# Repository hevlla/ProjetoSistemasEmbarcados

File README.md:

# Controlador do nível de água

## Introdução:

  O controlador de nível de água, é um projeto cujo objetivo é utilizar um microcontrolador que será o responsável pelo controle automático da bomba de água, mensurando com o auxílio de sensores, o nível de água em um tanque. Este sistema monitora o nível de água do tanque e liga a bomba automaticamente sempre que o tanque está vazio. A bomba é desligada quando o tanque superior ou recipiente está cheio. Aqui, o nível de água do tanque é indicado no LCD (Display de cristal líquido). Usando este sistema, podemos evitar o transbordamento da água.
  O presente trabalho apresenta uma solução prática para solucionar problemas relacionados ao controle do nível de água nos mais diversos reservatórios. Tendo em vista a dificuldade de acesso onde os reservatórios são instalados, em locais altos, torna-se difícil a visualização do seu conteúdo e consequentemente de seu controle; torna-se então indispensável a utilização de um sensor de nível de água não só para facilitar mas como também ao acrescentar a automatização, proporcionar uma melhor experiência para as pessoas que utilizam deste serviço.

## Estado da arte:

  O Sensor de Nível é um tipo de medidor feito para atuar em determinados pontos fixos de nível. Esses pontos fixos são valores de nível que, uma vez alcançados, exigem o desencadeamento de alguma ação necessária para a operação ou para a segurança do sistema em que o instrumento está inserido. Esses sensores podem ser utilizados para ligar uma bomba, acionar um alarme ou desencadear uma sequência de operações automáticas quando o nível atinge um ponto fixo, informando à eles através de ajustes determinados.
  Um Sensor de Nível é composto basicamente de duas partes: um detector de nível e um circuito de saída. O detector informa ao circuito de saída a presença ou ausência do nível em determinada posição. Já o circuito de saída se encarrega de alterar o estado de saída do sensor em função da informação transmitida pelo detector.

  - **Sensor de nível tipo bóia**
    É uma solução simples e amplamente utilizada no mercado devido a sua simplicidade e baixo custo de aplicação. Ele pode ser instalado tanto na horizontal quanto na vertical.  A forma mais utilizada é na parte lateral do tanque, horizontalmente. Quando o nível aumenta ou diminui, a boia se movimenta junto e, através de uma haste, é feito, magneticamente, o acionamento do contato.

  - **Sensor de nível capacitivo**
    Funciona como um capacitor. O sensor é uma das placas do capacitor e a parede metálica do tanque é a segunda. O que está entre eles é o material isolante. 
    A capacitância é a capacidade de armazenamento do capacitor. Isto depende das áreas da placa e de suas distância, além da constante dielétrica. Quando o tanque está com o nível zerado, existe apenas o ar como material isolante entre as placas. À medida que o produto começa a preencher o tanque, a capacitância é alterada. Ela é diretamente proporcional ao nível do tanque.

  - **Sensor de nível vibratório**
    Atua utilizando o amortecimento da vibração de uma haste só ou de duas hastes em forma de diapasão como meio de medir o nível. 
    O amortecimento mecânico acontece pela absorção de energia de vibração pela viscosidade de um líquido ou pela resistência de sólidos granulares ou em pó que entram em contato com uma ou mais hastes.
    O Sensor de Nível por vibração consiste em um garfo simétrico com duas extremidades. Na base do garfo há uma fina membrana com conexão a uma extensão em aço inoxidável que entra em contato com o processo. O garfo de vibração é excitado por uma frequência de ressonância por meio da membrana através de um cristal piezoelétrico.
    O garfo de vibração é projetado para, quando for imerso em um material, haver um deslocamento na sua frequência de ressonância de aproximadamente 10% a 20%. A frequência de ressonância é coletada por um receptor de cristal, e o seu deslocamento por um circuito específico tem por função comutar do tipo NA ou NF.
    De acordo com a configuração em que é executada, o Sensor de Nível vibratório poderá ser instalado lateralmente ou no topo do reservatório. Só é preciso ter cuidado com os cantos onde possam haver acúmulo de material e com as áreas em que ocorre a queda de material para a alimentação do reservatório.

  - Sensor de nível Condutivo
    O funcionamento desse tipo de sensor não possui restrição quanto à alta temperatura ou alta pressão. Assim, ele é indicado para vários tipos de medições de nível de líquidos, como água ou outros que não sejam condutivos.
    Seu princípio de funcionamento é simplificado! Ele se dá pela diferença de potencial (DDP) entre um eletrodo e outro no momento em que o eletrodo entrar em contato com o fluido.
    
  - Sensor de nível com RF Admitância
    É a solução mais eficiente para enfrentar os principais desafios da Medição de Nível, como incrustação, espuma, pó em suspensão e interfaces complexas, além de ser a maneira mais eficiente de evitar gargalos de produção com alarmes falsos, transbordamentos e/ou medição errônea.
    A RF Admitância utiliza um sinal de radiofrequência (RF) para, diante de um dos desafios, indicar a real presença ou ausência de produto, nível e/ou volume que está em contato com o elemento sensor do sensor.
    
## Quais sensores e atuadores serão utilizados e como serão utilizados: 

  - 2 Sensores de nível de água (boia), o sensor tipo boia funciona como uma chave magnética, entrando em curto quando a boia horizontal ou vertical é elevada, emitindo um sinal de que houve alteração naquele ponto. Serão dois sensores posicionados em níveis distintos (baixo e alto), sendo esse a faixa de intervalo a ser trabalhada e mensurada. 
  - 1 Arduino Uno.
  - 1 Display LCD com módulo I2C, será o responsável por informar como está a situação tanque “cheio, mediano ou crítico”. O módulo I2C reduz a quantidade de portas a serem preenchidas no arduino.
  - 1 contator ou relé, um contator suporta correntes maiores. Estes serão responsáveis por acionar a bomba.
  - Jumpers, resistores

## Especificações técnicas do microcontrolador: 
  O microcontrolador escolhido foi o Arduino Uno, logo após várias comparações entre custo e benefício, apesar deste, possuir menos quantidade de portas e uma memória flash 8 vezes menor ao compararmos com o Arduino Mega, concluímos que o arduino escolhido irá atender com êxito os objetivos propostos pelo projeto.    

  - Microcontrolador ATMEL ATMEGA328
  - Arquitetura: RISC
  - Comunicação é realizada pelo protocolo STK500

## Descrição do funcionamento do projeto:
  O controlador de nível de água, possui 2 sensores de nível tipo bóia que informaram três estados: cheio, mediano e crítico, este será o responsável por acionar o relé que ligará a bomba para encher a caixa da água até o estado cheio, onde será desligada.

## Link para a videoaula correspondente à explicação do circuito elétrico e o código utilizado no desenvolvimento do projeto:
  O vídeo está disponível no YouTube no seguinte endereço: https://youtu.be/xt-_fORybkc

## Artigos de referência:
  Controle de nível de água em relação a rio - https://bityli.com/8xCLy
  Automatização de cisternas e caixa d’água de condomínios via CLP - http://repositorio.utfpr.edu.br/jspui/handle/1/16909

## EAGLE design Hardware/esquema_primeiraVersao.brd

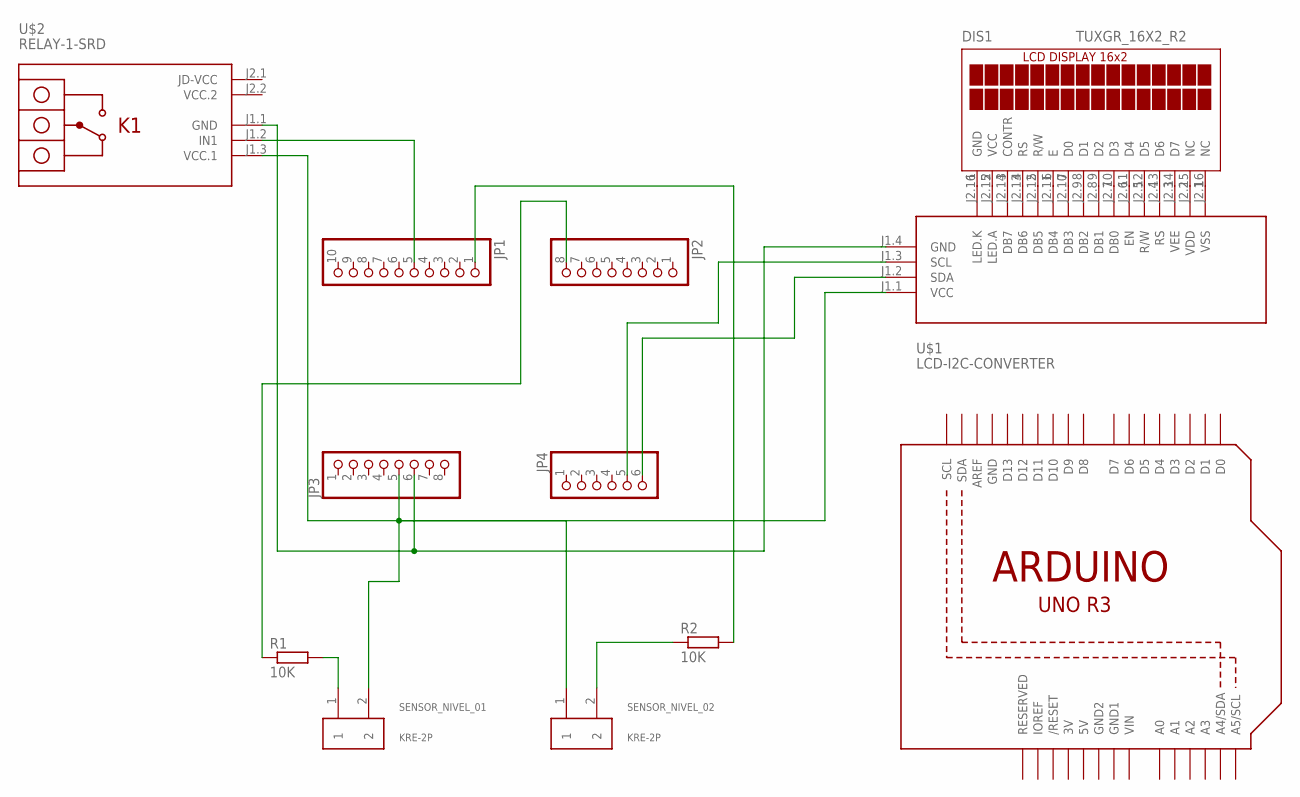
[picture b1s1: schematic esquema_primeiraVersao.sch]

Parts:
DIS1: TUXGR_16X2_R2
JP1: PINHD-1X10; 1X10
JP2, JP3: PINHD-1X8; 1X08
JP4: PINHD-1X6; 1X06
R1, R2: 10K; 0204/5
SENSOR_NIVEL_01, SENSOR_NIVEL_02: KRE-2P
U1: ARDUINOR3-BPLACE
U$1: LCD-I2C-CONVERTER
U$2: RELAY-1-SRD

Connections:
3V: U1.3V
5V: U1.5V
GND: U1.GND
GND1: U1.GND1
GND2: U1.GND2
unnamed: DIS1.1 (GND), U$1.J2.16 (LED.K)
unnamed: DIS1.2 (VCC), U$1.J2.15 (LED.A)
unnamed: DIS1.3 (CONTR), U$1.J2.14 (DB7)
unnamed: DIS1.4 (RS), U$1.J2.13 (DB6)
unnamed: DIS1.5 (R/W), U$1.J2.12 (DB5)
unnamed: DIS1.6 (E), U$1.J2.11 (DB4)
unnamed: DIS1.7 (D0), U$1.J2.10 (DB3)
unnamed: DIS1.8 (D1), U$1.J2.9 (DB2)
unnamed: DIS1.9 (D2), U$1.J2.8 (DB1)
unnamed: DIS1.10 (D3), U$1.J2.7 (DB0)
unnamed: DIS1.11 (D4), U$1.J2.6 (EN)
unnamed: DIS1.12 (D5), U$1.J2.5 (R/W)
unnamed: DIS1.13 (D6), U$1.J2.4 (RS)
unnamed: DIS1.14 (D7), U$1.J2.3 (VEE)
unnamed: DIS1.15 (NC), U$1.J2.2 (VDD)
unnamed: DIS1.16 (NC), U$1.J2.1 (VSS)
unnamed: JP2.8, R1.1
unnamed: R1.2, SENSOR_NIVEL_01.1
unnamed: JP3.5, SENSOR_NIVEL_01.2, SENSOR_NIVEL_02.1, U$1.J1.1 (VCC), U$2.J1.3 (VCC.1)
unnamed: R2.1, SENSOR_NIVEL_02.2
unnamed: JP1.1, R2.2
unnamed: JP1.5, U$2.J1.2 (IN1)
unnamed: JP3.6, U$1.J1.4 (GND), U$2.J1.1 (GND)
unnamed: JP4.6, U$1.J1.2 (SDA)
unnamed: JP4.5, U$1.J1.3 (SCL)
VCC.2: U$2.J2.2 (VCC.2)
VIN: U1.VIN

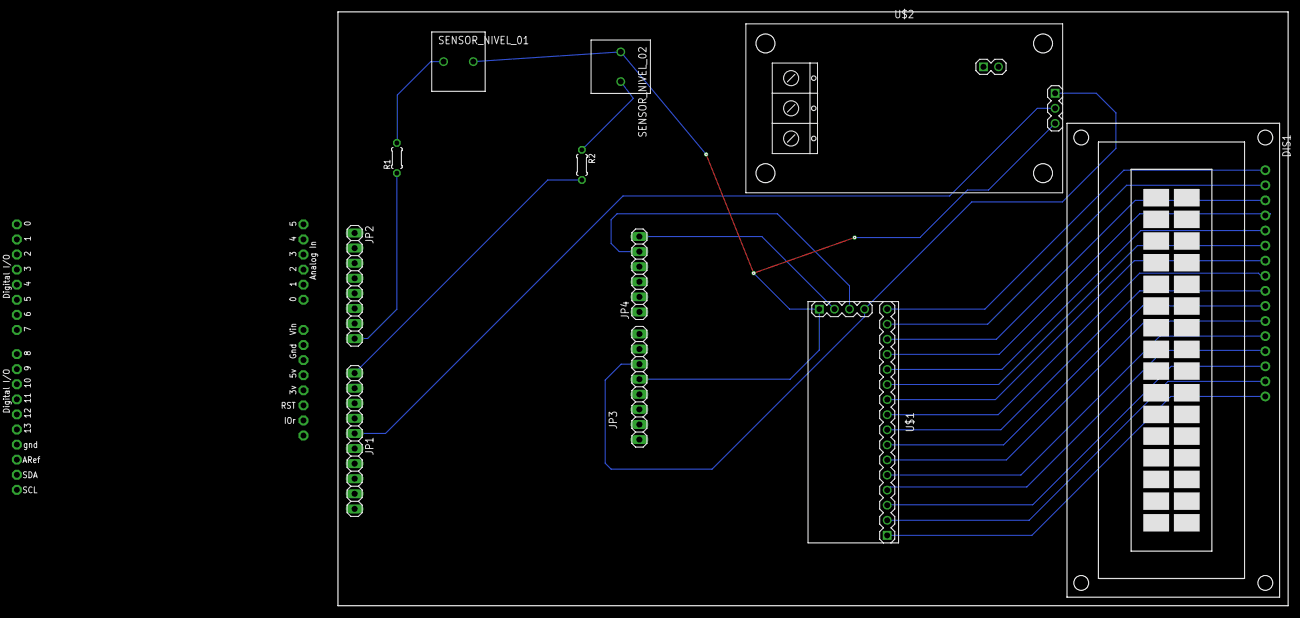
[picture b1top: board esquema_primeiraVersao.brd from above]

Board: 2 copper layers, 160.0 x 100.0 mm, 12 parts (0 on the bottom side), 25 nets.

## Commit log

2021-05-25 Descrição
2021-05-28 Inserindo o link da videoaula que está no YouTube

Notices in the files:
parts and their libraries:
diy-modules: Released under the Creative Commons Attribution 4.0 International License: http://creativecommons.org/licenses/by/4.0
